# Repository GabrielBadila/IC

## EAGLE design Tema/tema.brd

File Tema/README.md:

# Amplificator de buzunar CMOY (Romanian language)

	Ingineria calculatoarelor

	Tema - Amplificator de buzunar CMOY

	Badila Gabriel Alin
	333 CA

	============================================================================

	Arhiva temei contine trei fisiere: tema.sch (schematicul), tema.brd 
	(board-ul) si acest Readme.

	In fisierul tema.sch am realizat schema electrica a amplificatorului CMOY 
	cu ajutorul bibliotecilor: rhine-misc.lbr si project-box.lbr, prevazute in 
	documentatia temei, pe baza schemei si a listei de piese, prevazute de 
	asemenea in documentatia temei. Au fost realizate trei circuite: partea de 
	alimentare, canalul stang, respectiv canalul drept al semnalului, ultimele 
	doua fiind comasate intr-un singur circuit din cauza jack-urilor de 
	input/output care legau cele doua circuite. Mentionez ca circuitele au fost 
	realizate in acelasi fisier, deoarece liniile de supply si ground sunt 
	legate in momentul adaugarii surselor/GND-ului, asa cum este precizat si in 
	cerinta temei. Am verificat apoi ca ERC sa nu genereze nicio eroare/warning.
	
	In fisierul tema.brd am realizat partea de board a temei. Am luat piesele 
	aflate la gramada si le-am asezat in chenarul de proiectare al board-ului 
	astfel incat numarul de suprapuneri al conexiunilor dintre piese sa fie 
	minim. Apoi am selectat auto-route si am ales una dintre rutele generate de 
	tool. Am verificat cu DRC, si dupa cum era de asteptat nu exista nicio 
	eroare. Am activat optiunile prevazute in cerinta temei (distantanta intre 
	oricare doua componente = 10mil, verificarea pentru gaurile de burghiu = 
	10mil si dimensiunea pad-urilor sa fie mai mare cu 50% decat valoarea 
	implicita) si am rulat din nou DRC. In urma modificarilor facute era si 
	normal sa apara erori (erorile aparute faceau referire la distanta dintre 
	componente). Am realizat modificarile necesare rutelor, iar DRC nu a mai 
	generat nicio eroare/warning.

	============================================================================

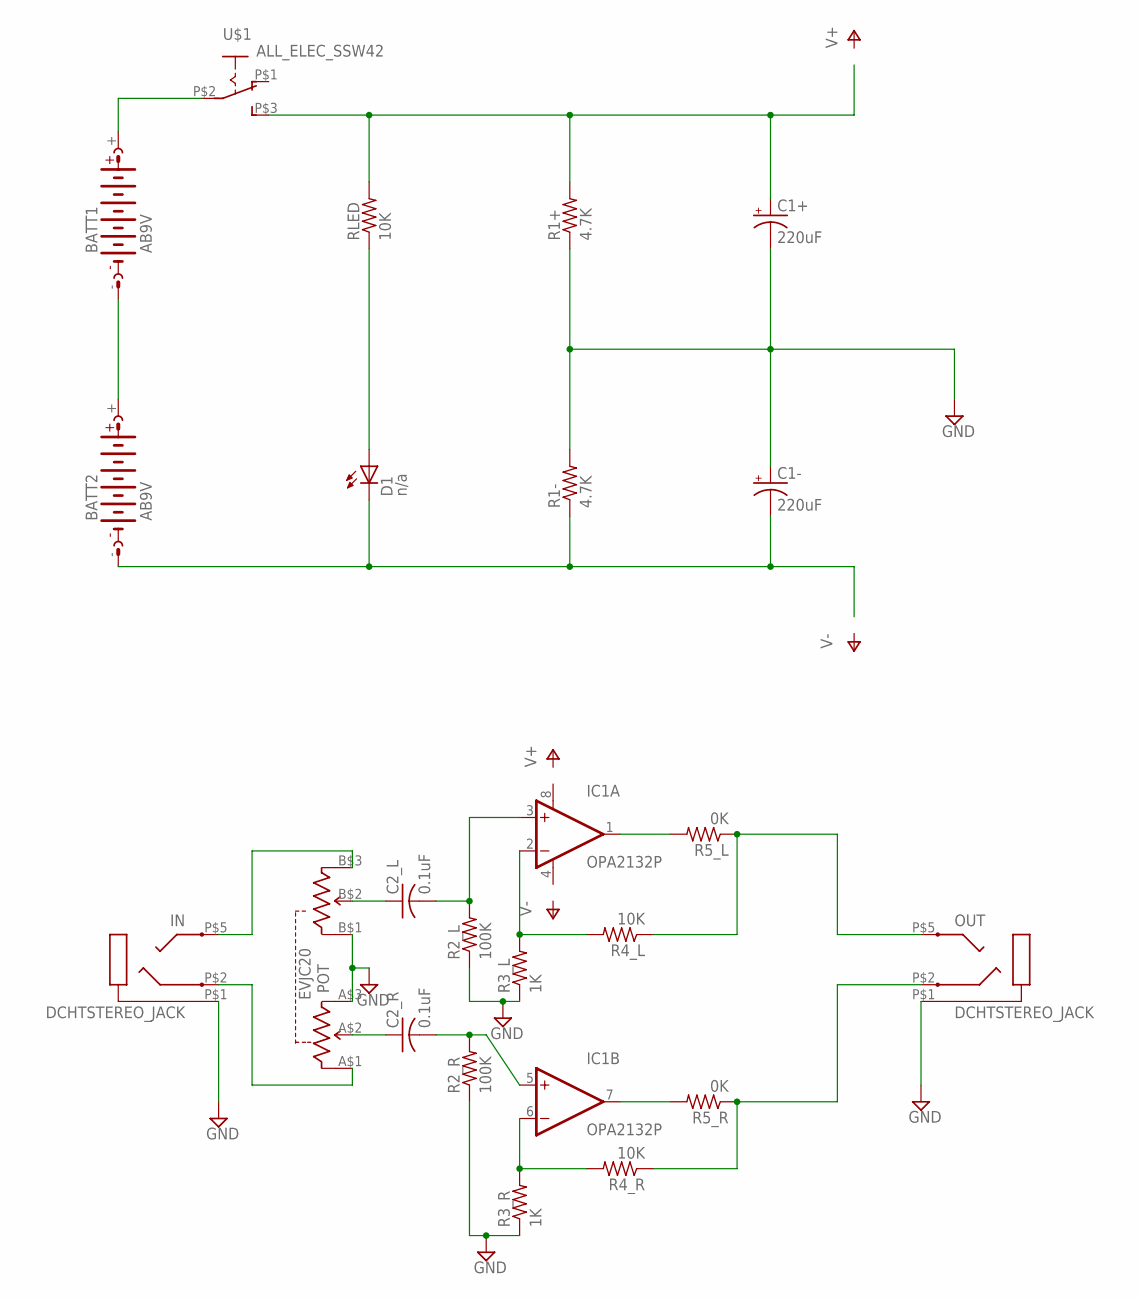
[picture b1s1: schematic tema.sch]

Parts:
BATT1, BATT2: AB9V
C1+, C1-: 220uF; E3,5-8
C2_L, C2_R: 0.1uF; C075-052X106
D1: n/a; LED5MM
IC1: OPA2132P; DIL08
IN: DCHTSTEREO_JACK; DCHTSTJACK
OUT: DCHTSTEREO_JACK; DCHTSTJACK
POT: EVJC20; PC16D
R1+, R1-: 4.7K; 0207/5V
R2_L, R2_R: 100K; 0207/7
R3_L, R3_R: 1K; 0207/7
R4_L, R4_R: 10K; 0207/7
R5_L, R5_R: 0K; 0207/7
RLED: 10K; 0207/5V
U$1: ALL_ELEC_SSW42; SSW-42

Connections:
GND: C1+.-, C1-.+, IN.P$1 (1), OUT.P$1 (1), POT.A$3 (1E), POT.B$1 (2A), R1+.1, R1-.2, R2_L.1, R2_R.1, R3_L.1, R3_R.1
unnamed: BATT1.-, BATT2.+
unnamed: BATT1.+, U$1.P$2
unnamed: C1+.+, R1+.2, RLED.2, U$1.P$3 (S)
unnamed: BATT2.-, C1-.-, D1.K (C), R1-.1
unnamed: D1.A, RLED.1
unnamed: IN.P$2 (2), POT.A$1 (1A)
unnamed: IN.P$5 (5), POT.B$3 (2E)
unnamed: C2_R.1, POT.A$2 (1S)
unnamed: C2_L.1, POT.B$2 (2S)
unnamed: C2_L.2, IC1.3 (+IN), R2_L.2
unnamed: IC1.2 (-IN), R3_L.2, R4_L.2
unnamed: C2_R.2, IC1.5 (+IN), R2_R.2
unnamed: IC1.6 (-IN), R3_R.2, R4_R.2
unnamed: IC1.7 (OUT), R5_R.2
unnamed: IC1.1 (OUT), R5_L.2
unnamed: OUT.P$2 (2), R4_R.1, R5_R.1
unnamed: OUT.P$5 (5), R4_L.1, R5_L.1
V+: IC1.8 (V+)
V-: IC1.4 (V-)

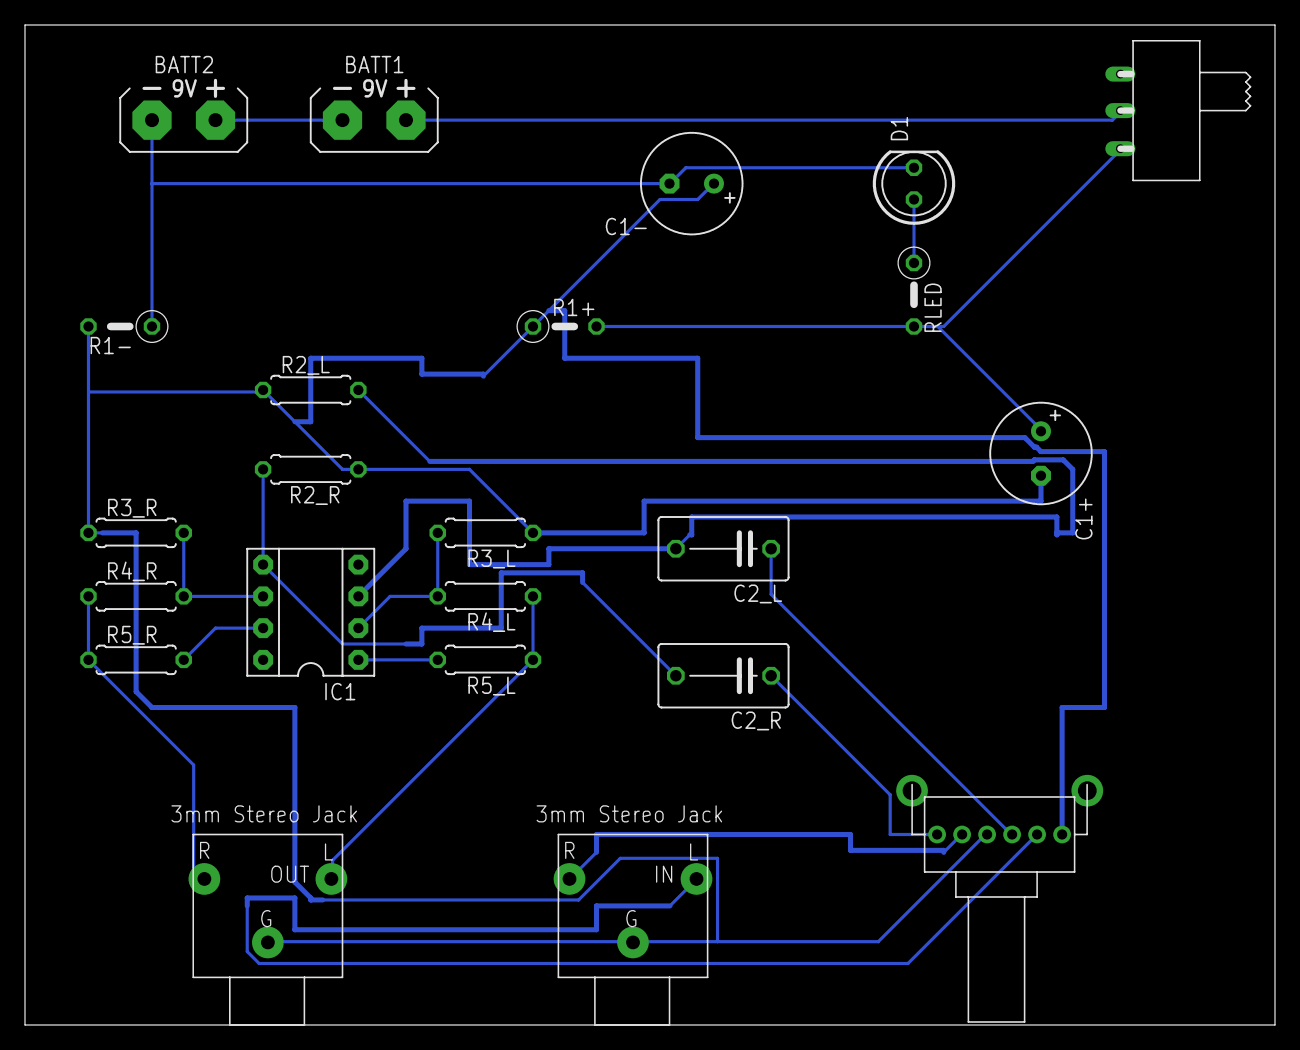
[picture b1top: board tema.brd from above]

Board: 2 copper layers, 100.0 x 80.0 mm, 23 parts (0 on the bottom side), 18 nets.

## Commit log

2017-11-05 Added "Tema"
